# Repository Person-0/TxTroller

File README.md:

# **TxTroller**
*A Radio Receiver-to-USB HID Gamepad Adapter.*

## Build Photos

## Demo Video 
> Click to open in YouTube
<div align="left">
      
</div>

# What is this?
This is a simple adapter that will allow older-style Radio transmitter / receiver combos to be used as video-game controllers using the USB HID Gamepad device class.

Watch me crash quads using TxTroller: [youtube video link](https://www.youtube.com/watch?v=WwyzCUGAeks)

## Hardware
For the initial stages, this is being developed for the [`Radiolink R8EF`](https://www.radiolink.com/r8ef) receiver, which is an 8-channel receiver operating on the 2.4GHz frequency band.

As for the transmitter that will be the actual gamepad, It will be the [`Radiolink T8FB`](https://www.radiolink.com/t8fb) transmitter, which is a 2.4GHz 8 Channels RC Remote Transmitter.

The microcontroller that will be responsible for translating the SBUS signals from the receiver to the USB device class is the [`XIAO RP2040`](https://wiki.seeedstudio.com/XIAO-RP2040/) due to it's small footprint and easy-to-use C/C++ SDK.

## PCB

The PCB has been designed using KiCAD 9.0. It is a 2 layer PCB with both top and bottom having thick signal traces and a ground fill.

PCB Schematics:

PCB layout:

PCB Preview:

## 3D Case

The case has been designed in Fusion 360, with the `.f3z` available in the [/CAD](./CAD/) directory, along with the exported `.step` files of the top and bottom parts of the case in [/CAD/exports](./CAD/exports).

The case looks like this:

The case has side extrusions for friction-fitting the top and bottom part of the case together.

## Firmware
*Originally modified from [raspberrypi/pico-examples/tree/master/usb/device/dev_hid_composite
](https://github.com/raspberrypi/pico-examples/tree/master/usb/device/dev_hid_composite).*

Checkout the [Firmware directory](./Firmware/) to view more information on button mappings, firmware compiling / flashing and testing the data received from the receiver.

## Ordering, BOM & 3d Printing

The PCB contains no SMD components or any other component that cannot be soldered using a normal soldering iron, hence no PCBA is required.

The PCB gerber .zip file is available in [PCB/exports/](./PCB/exports/).

### BOM Table
---

| S.No | Item Name        | Description                    | Product URL                                                                              | Qty | Unit Price ($) | Effective Price ($) |
| ---: | ---------------- | ------------------------------ | ---------------------------------------------------------------------------------------- | --: | -------------: | ------------------: |
|    1 | XIAO RP2040      | RP2040 Microcontroller         | [XIAO RP2040](https://robocraze.com/products/seeed-studio-xiao-rp2040-development-board) |   1 |           6.14 |                6.14 |
|    2 | PCB              | PCB manufacturing cost (5 qty) | [Lion Circuits](https://www.lioncircuits.com/quote)                                      |   1 |           9.84 |                9.84 |
|    3 | 1k Ohm Resistor  | 1k Ohm Resistor - Pack of 10   | [1k Resistor Pack](https://robocraze.com/products/1k-resistor-pack-of-10)                |   1 |           0.13 |                0.13 |
|    4 | 10k Ohm Resistor | 10k Ohm Resistor - Pack of 10  | [10k Resistor Pack](https://robocraze.com/products/10k-resistor-pack-of-10)              |   1 |           0.14 |                0.14 |
|    5 | 100 Ohm Resistor | 100 Ohm Resistor - Pack of 10  | [100 Ohm Resistor Pack](https://robocraze.com/products/100-ohm-resistor-pack-of-10)      |   1 |           0.16 |                0.16 |
|      |                  |                                |                                                                                          |     |      **Total** |           **16.41$** |

---

> *Note that the PCB states 150ohm resistor but we have only added 100ohm, this is because we can arrange 3 100 ohm resistors in such a way that the effective resistance becomes 150ohms (2parallel+1series).*

As for the 3d prints, the following files need to be printed **separately**:
- [CAD/exports/TxTroller_lid.step](./CAD/exports/TxTroller_lid.step)
- [CAD/exports/TxTroller_bottom.step](./CAD/exports/TxTroller_bottom.step)

Since they are designed to be friction fitted, no screws or heatset-inserts are needed.

## Assembly Instructions
1. Get the PCB manufactured via any PCB fab (I used [lioncircuits.com/](https://www.lioncircuits.com/))
2. Solder the transistor, LED, resistors, headers and then finally the MCU. (This order is preferred so as to not let other components get damaged due to less space)
3. Flash the firmware, connect your receiver and test whether the device is working fine.
4. Get the case 3d printed, set the PCB inside the bottom part of the case, close it via the lid.
5. If the case is loose, use a rubber band to firmly hold it in place. Connect the receiver and place it beneath the bottom part of the case.
6. Again use something like a rubber badn to hold the receiver firmly in place.
7. Build finished!

## Credits
- https://github.com/controllercustom/dinput_tinyusb
- https://www.thingiverse.com/thing:6989033
- https://www.reddit.com/r/embedded/comments/1m6d1ei/gamepad_using_tinyusb_on_raspberry_pi_pico/
- https://github.com/gdsports/gamepad_tinyusb
- https://github.com/raspberrypi/pico-examples/tree/master/usb/device/dev_hid_composite

## Thank You! 😼💖

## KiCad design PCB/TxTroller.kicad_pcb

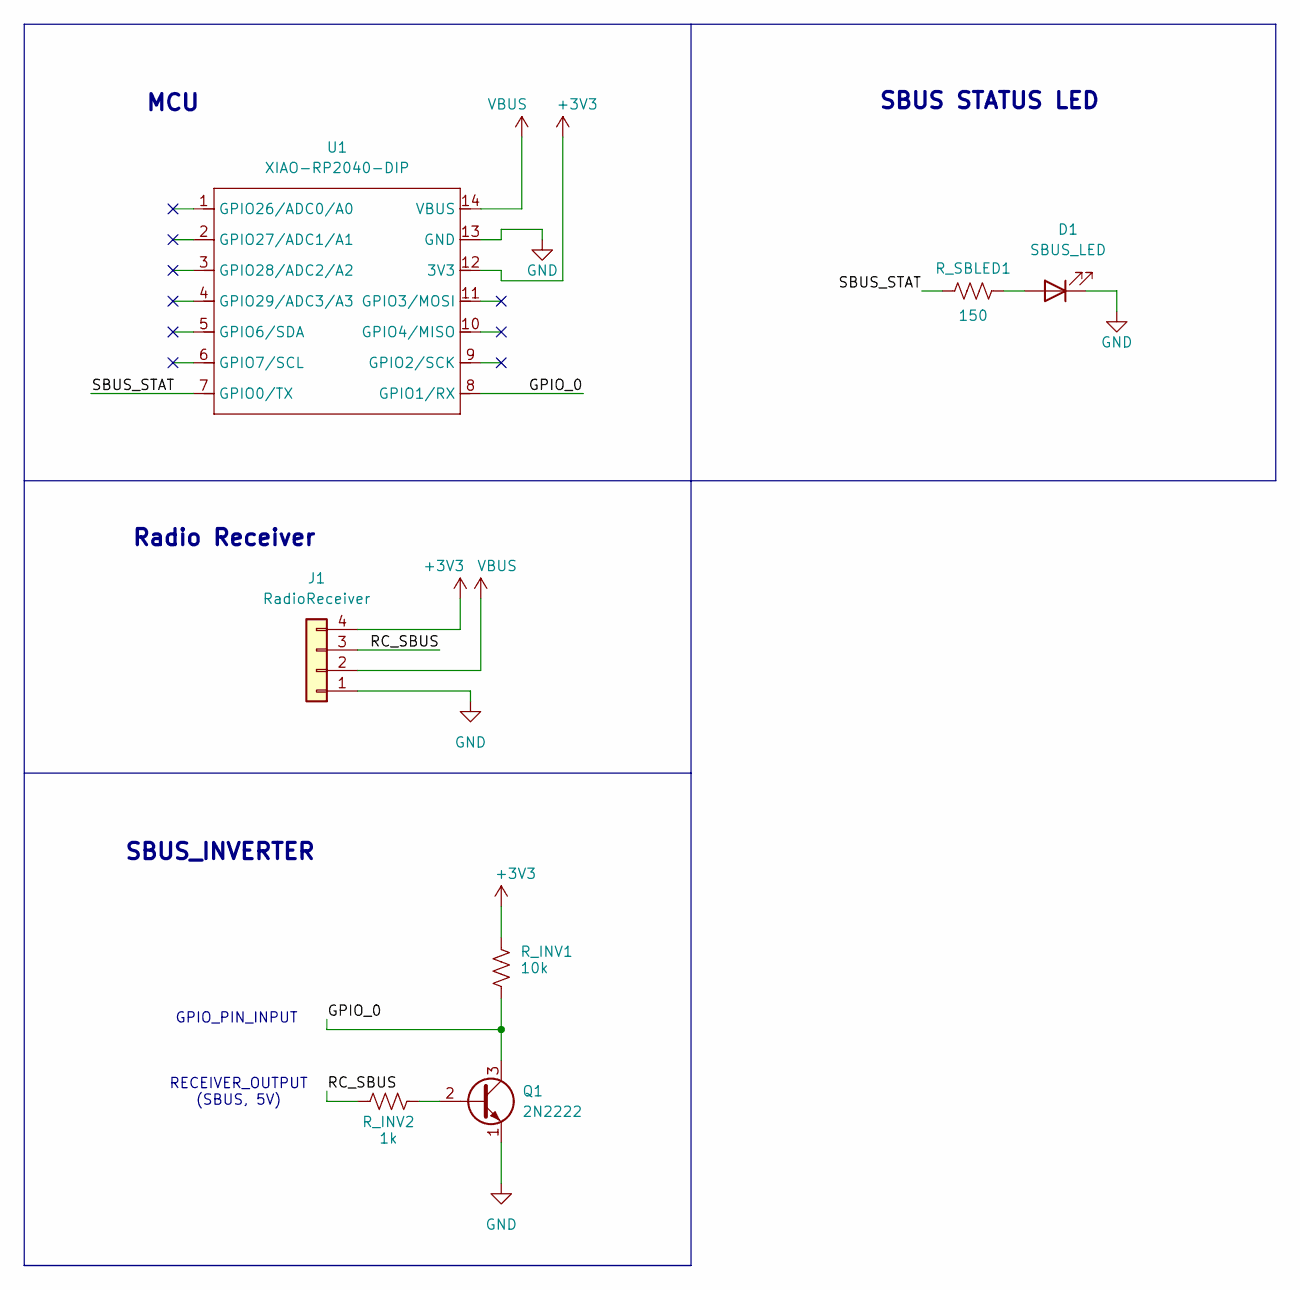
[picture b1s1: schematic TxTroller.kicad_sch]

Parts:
D1: SBUS_LED; PinHeader_1x02_P2.54mm_Vertical
J1: RadioReceiver; PinHeader_1x04_P2.54mm_Vertical
Q1: 2N2222; PinHeader_1x03_P2.54mm_Vertical
R_INV1: 10k; PinHeader_1x02_P2.54mm_Vertical
R_INV2: 1k; PinHeader_1x02_P2.54mm_Vertical
R_SBLED1: 150; PinHeader_1x02_P2.54mm_Vertical
U1: XIAO-RP2040-DIP

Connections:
+3V3: J1.4, R_INV1.1, U1.12 (3V3)
/<NO NET>: Q1.3 (C), R_INV1.2, U1.8 (GPIO1/RX)
/RC_SBUS: J1.3, R_INV2.2
/SBUS_STAT: R_SBLED1.2, U1.7 (GPIO0/TX)
GND: D1.1 (K), J1.1, Q1.1 (E), U1.13 (GND)
unnamed: D1.2 (A), R_SBLED1.1
unnamed: Q1.2 (B), R_INV2.1
VBUS: J1.2, U1.14 (VBUS)

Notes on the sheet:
MCU
SBUS_INVERTER
SBUS STATUS LED
GPIO_PIN_INPUT
RECEIVER_OUTPUT (SBUS, 5V)
Radio Receiver

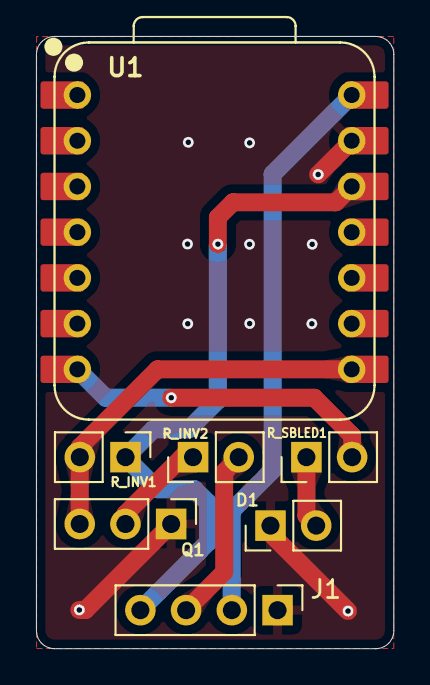
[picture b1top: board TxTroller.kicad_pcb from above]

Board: 2 copper layers, 19.9 x 34.0 mm, 7 parts (0 on the bottom side), 8 nets.
